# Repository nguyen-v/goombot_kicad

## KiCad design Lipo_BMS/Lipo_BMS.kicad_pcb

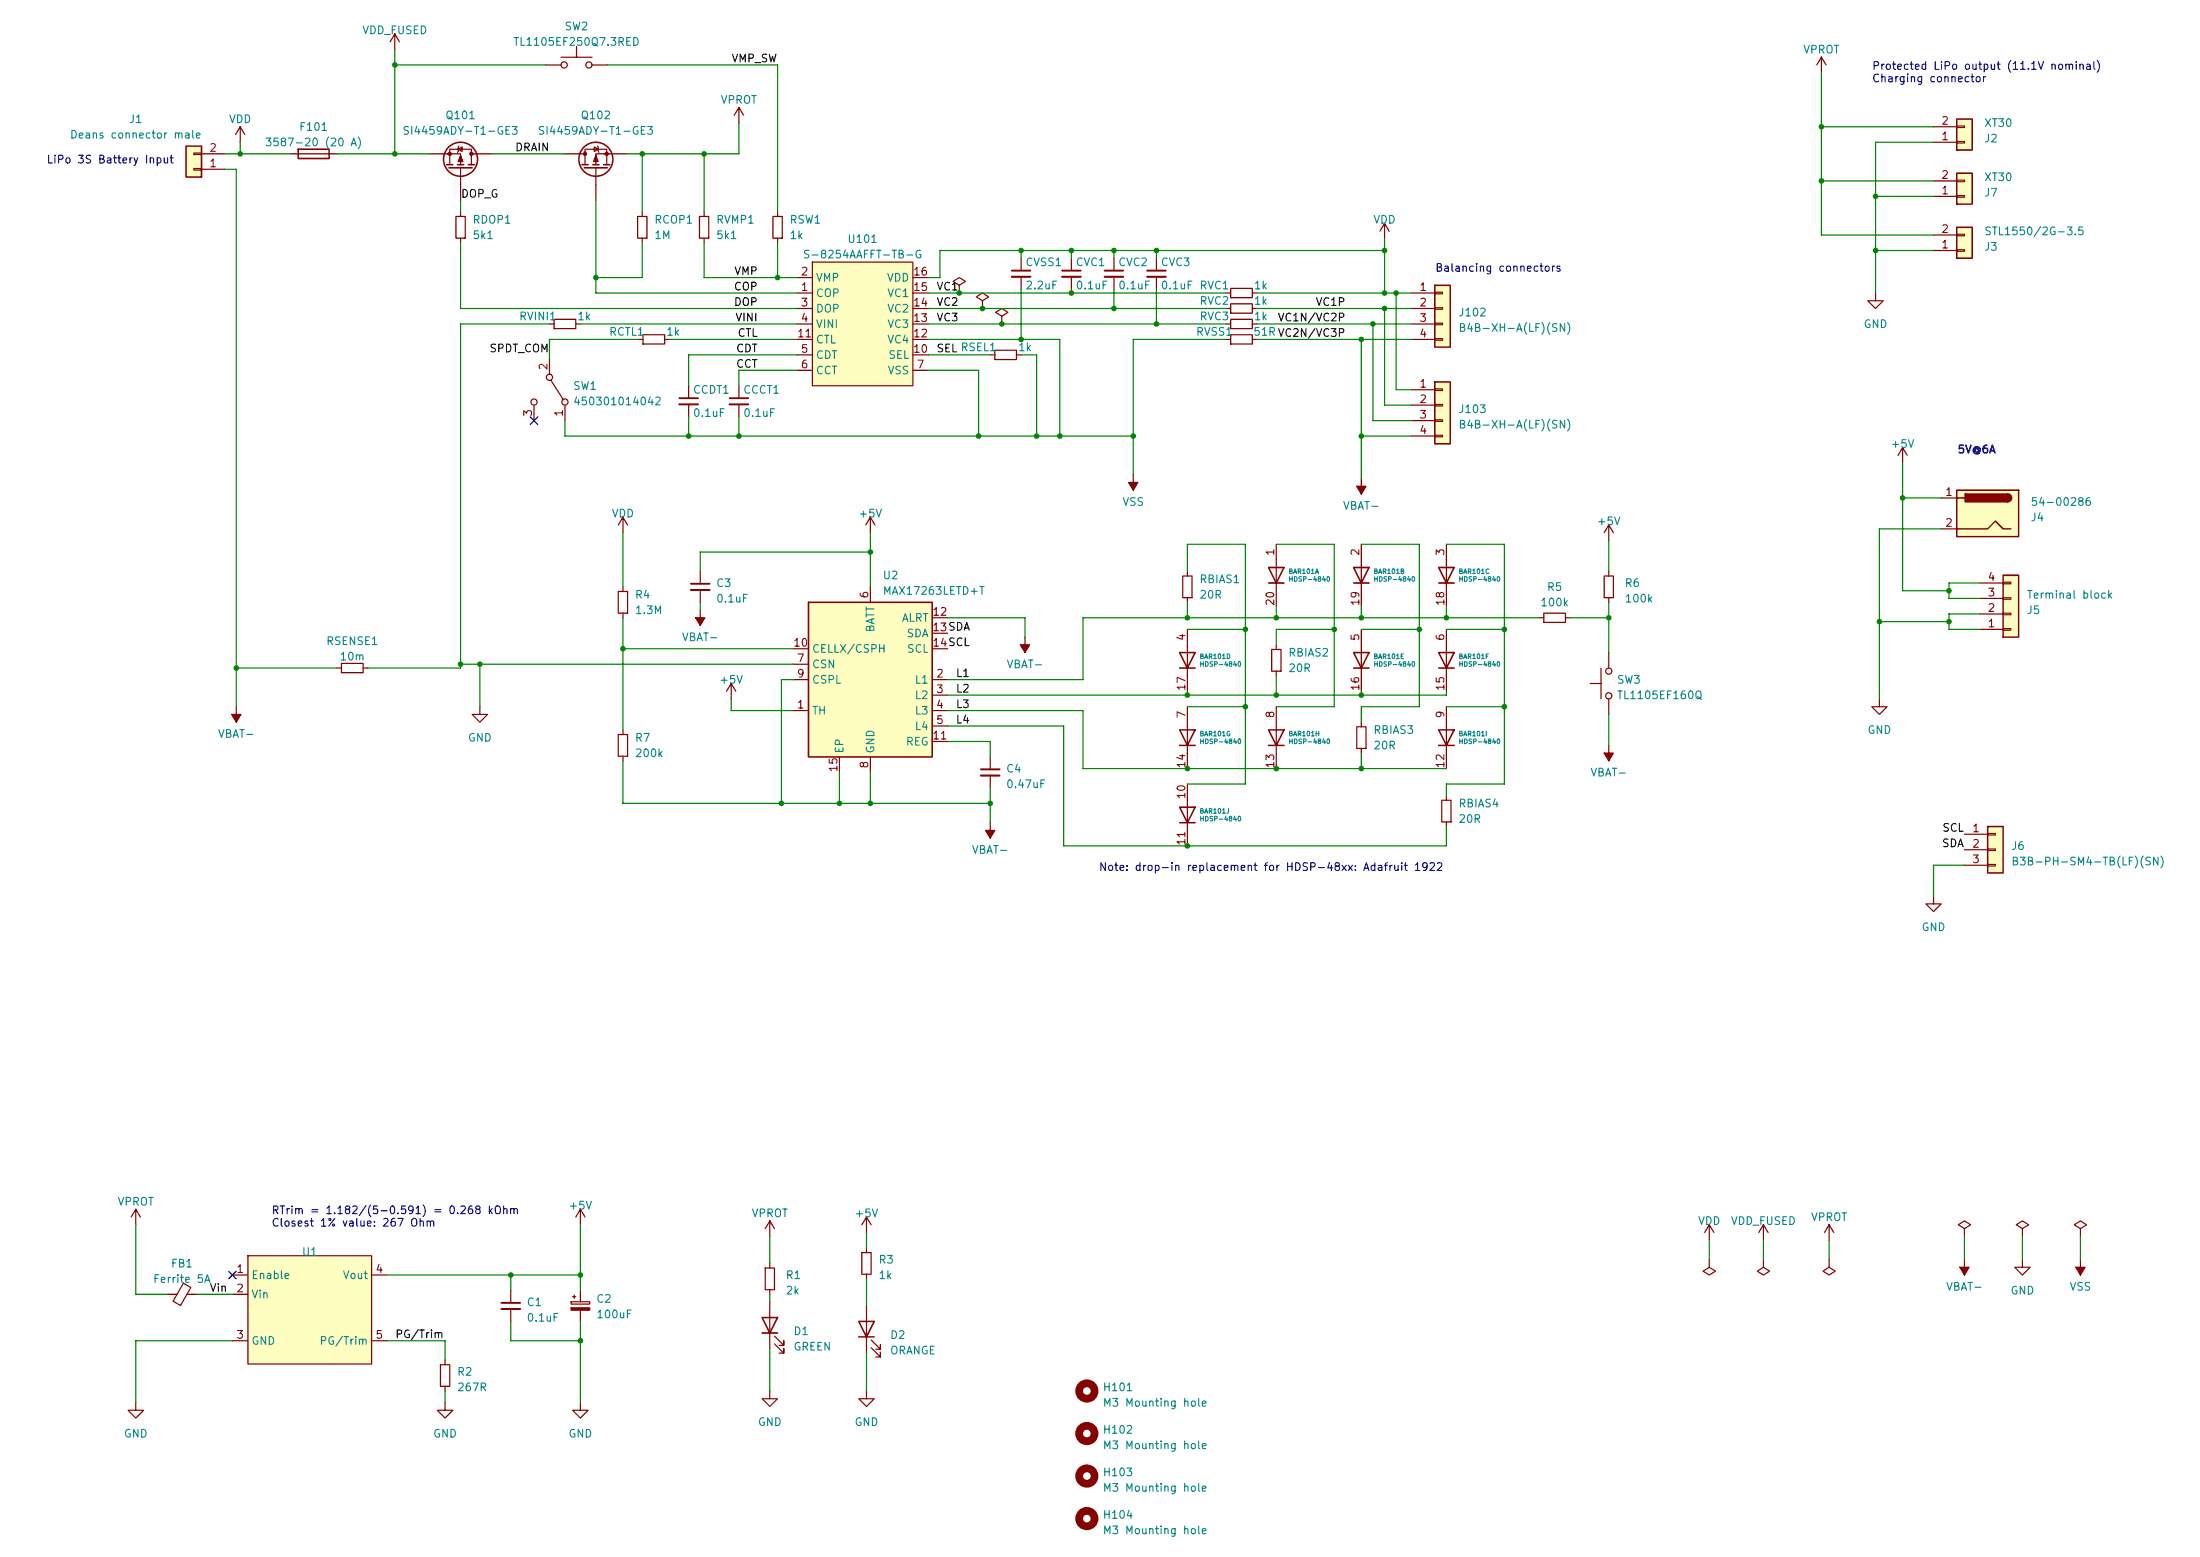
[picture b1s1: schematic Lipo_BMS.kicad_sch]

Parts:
BAR101: HDSP-4840
C1, C3: 0.1uF; C_0603_1608Metric
C2: 100uF; C_1210_3225Metric
C4: 0.47uF; C_0603_1608Metric
CCCT1: 0.1uF; C_0603_1608Metric
CCDT1: 0.1uF; C_0603_1608Metric
CVC1, CVC2, CVC3: 0.1uF; C_0603_1608Metric
CVSS1: 2.2uF; C_0603_1608Metric
D1: GREEN; LED_0603_1608Metric
D2: ORANGE; LED_0603_1608Metric
F101: 3587-20 (20 A); 3587
FB1: Ferrite 5A; L_0603_1608Metric
H101, H102, H103, H104: M3 Mounting hole; MountingHole_3.2mm_M3_Pad
J1: Deans connector male; DEANS
J2, J7: XT30; AMASS_XT30U-M_1x02_P5.0mm_Vertical
J3: STL1550/2G-3.5; STL1550-2
J4: 54-00286
J5: Terminal block; TerminalBlock_Phoenix_MPT-0,5-4-2.54_1x04_P2.54mm_Horizontal
J6: B3B-PH-SM4-TB(LF)(SN); JST_PH_B3B-PH-SM4-TB_1x03-1MP_P2.00mm_Vertical
J102, J103: B4B-XH-A(LF)(SN); JST_XH_B4B-XH-A_1x04_P2.50mm_Vertical
Q101, Q102: SI4459ADY-T1-GE3; SOIC-8_3.9x4.9mm_P1.27mm
R1: 2k; R_0603_1608Metric
R2: 267R; R_0603_1608Metric
R3: 1k; R_0603_1608Metric
R4: 1.3M; R_0603_1608Metric
R5, R6: 100k; R_0603_1608Metric
R7: 200k; R_0603_1608Metric
RBIAS1, RBIAS2, RBIAS3, RBIAS4: 20R; R_0603_1608Metric
RCOP1: 1M; R_0603_1608Metric
RCTL1: 1k; R_0603_1608Metric
RDOP1: 5k1; R_0603_1608Metric
RSEL1: 1k; R_0603_1608Metric
RSENSE1: 10m; R_1206_3216Metric
RSW1: 1k; R_0603_1608Metric
RVC1, RVC2, RVC3: 1k; R_0603_1608Metric
RVINI1: 1k; R_0603_1608Metric
RVMP1: 5k1; R_0603_1608Metric
RVSS1: 51R; R_0603_1608Metric
SW1: 450301014042
SW2: TL1105EF250Q7.3RED; SW_PUSH_6mm_H7.3mm
SW3: TL1105EF160Q; SW_PUSH_6mm_H7.3mm
U1: LDO06C-005W05-HJ
U2: MAX17263LETD+T; DFN-14-1EP_3x3mm_P0.4mm_EP1.78x2.35mm
U101: S-8254AAFFT-TB-G; TSSOP-16_4.4x5mm_P0.65mm

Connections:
+5V: C1.1, C2.1, C3.1, J4.1, J5.3, J5.4, R3.1, R6.2, U1.4 (Vout), U2.1 (TH), U2.6 (BATT)
/CCT: CCCT1.1, U101.6 (CCT)
/CDT: CCDT1.1, U101.5 (CDT)
/COP: Q102.4 (G), RCOP1.1, U101.1 (COP)
/CTL: RCTL1.2, U101.11 (CTL)
/DOP: RDOP1.1, U101.3 (DOP)
/DOP_G: Q101.4 (G), RDOP1.2
/DRAIN: Q101.5 (D), Q101.6 (D), Q101.7 (D), Q101.8 (D), Q102.5 (D), Q102.6 (D), Q102.7 (D), Q102.8 (D)
/L1: BAR101.18 (K), BAR101.19 (K), BAR101.20 (K), R5.1, RBIAS1.1, U2.2 (L1)
/L2: BAR101.15 (K), BAR101.16 (K), BAR101.17 (K), RBIAS2.1, U2.3 (L2)
/L3: BAR101.12 (K), BAR101.13 (K), BAR101.14 (K), RBIAS3.1, U2.4 (L3)
/L4: BAR101.11 (K), RBIAS4.1, U2.5 (L4)
/PG/Trim: R2.1, U1.5 (PG/Trim)
/SCL: J6.1, U2.14 (SCL)
/SDA: J6.2, U2.13 (SDA)
/SEL: RSEL1.1, U101.10 (SEL)
/SPDT_COM: RCTL1.1, SW1.2 (B)
/VC1: CVC1.2, RVC1.1, U101.15 (VC1)
/VC1N/VC2P: J102.3, J103.3, RVC3.2
/VC1P: J102.2, J103.2, RVC2.2
/VC2: CVC2.2, RVC2.1, U101.14 (VC2)
/VC3: CVC3.2, RVC3.1, U101.13 (VC3)
/VINI: RVINI1.2, U101.4 (VINI)
/VMP: RSW1.1, RVMP1.1, U101.2 (VMP)
/VMP_SW: RSW1.2, SW2.2
/Vin: FB1.2, U1.2 (Vin)
GND: C1.2, C2.2, D1.1 (K), D2.1 (K), J2.1, J3.1, J4.2, J5.1, J5.2, J6.3, J7.1, R2.2, RSENSE1.2, RVINI1.1, U1.3 (GND), U2.7 (CSN)
unnamed: BAR101.1 (A), BAR101.8 (A), RBIAS2.2
unnamed: BAR101.2 (A), BAR101.5 (A), RBIAS3.2
unnamed: BAR101.3 (A), BAR101.6 (A), BAR101.9 (A), RBIAS4.2
unnamed: BAR101.4 (A), BAR101.7 (A), BAR101.10 (A), RBIAS1.2
unnamed: D1.2 (A), R1.2
unnamed: D2.2 (A), R3.2
unnamed: R5.2, R6.1, SW3.2
unnamed: R4.1, R7.2, U2.10 (CELLX/CSPH)
unnamed: C4.1, U2.11 (REG)
VBAT-: C3.2, C4.2, J1.1, J102.4, J103.4, R7.1, RSENSE1.1, RVSS1.2, SW3.1, U2.8 (GND), U2.9 (CSPL), U2.12 (ALRT), U2.15 (EP)
VDD: CVC1.1, CVC2.1, CVC3.1, CVSS1.1, F101.1, F101.2, J1.2, J102.1, J103.1, R4.2, RVC1.2, U101.16 (VDD)
VDD_FUSED: F101.3, F101.4, Q101.1 (S), Q101.2 (S), Q101.3 (S), SW2.1
VPROT: FB1.1, J2.2, J3.2, J7.2, Q102.1 (S), Q102.2 (S), Q102.3 (S), R1.1, RCOP1.2, RVMP1.2
VSS: CCCT1.2, CCDT1.2, CVSS1.2, RSEL1.2, RVSS1.1, SW1.1 (A), U101.7 (VSS), U101.12 (VC4)

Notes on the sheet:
RTrim = 1.182/(5-0.591) = 0.268 kOhm Closest 1% value: 267 Ohm
5V@6A
Note: drop-in replacement for HDSP-48xx: Adafruit 1922
Balancing connectors
Protected LiPo output (11.1V nominal) Charging connector
LiPo 3S Battery Input

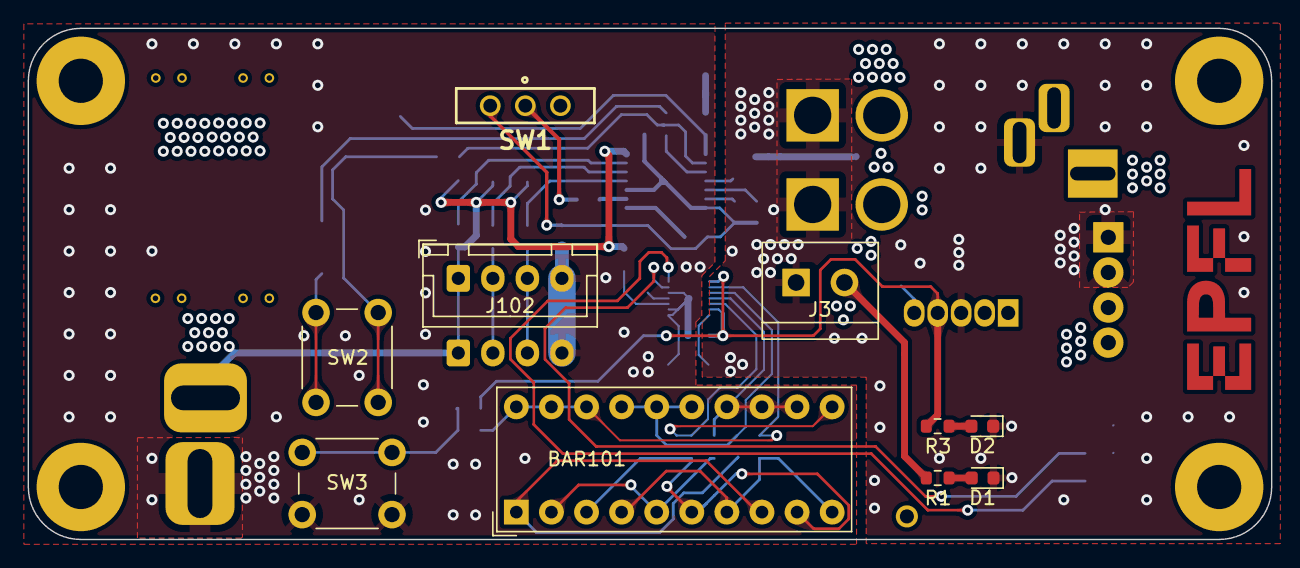
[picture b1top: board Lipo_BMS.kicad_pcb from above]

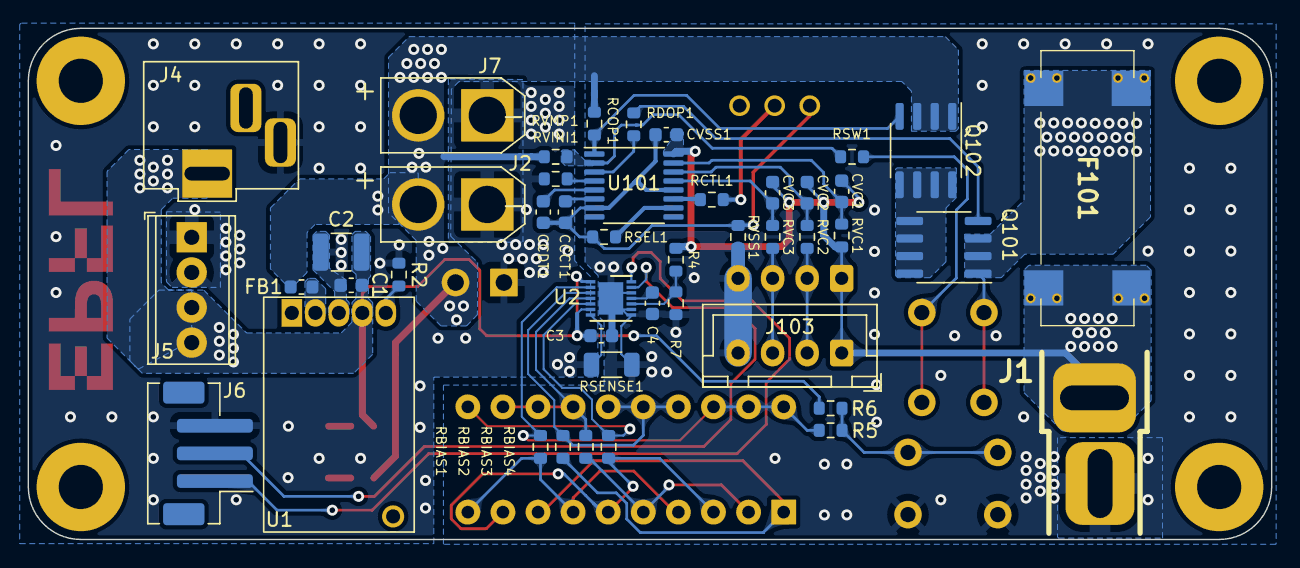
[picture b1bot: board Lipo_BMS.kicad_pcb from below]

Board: 2 copper layers, 90.0 x 37.0 mm, 81 parts (56 on the bottom side), 41 nets.

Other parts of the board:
kibuzzard-643EAC98: G***; kibuzzard-643EAC98
kibuzzard-643EACB8: G***; kibuzzard-643EACB8
kibuzzard-643EACE6, kibuzzard-643EACE6#2, kibuzzard-643EACE6#3, kibuzzard-643EACE6#4: G***; kibuzzard-643EACE6
kibuzzard-643EACF0, kibuzzard-643EACF0#2: G***; kibuzzard-643EACF0
kibuzzard-643EAD40: G***; kibuzzard-643EAD40
kibuzzard-643EADF2: G***; kibuzzard-643EADF2
kibuzzard-643EAE00: G***; kibuzzard-643EAE00
kibuzzard-643EAE23: G***; kibuzzard-643EAE23
kibuzzard-643EAF8C, kibuzzard-643EAF8C#2: G***; kibuzzard-643EAF8C
kibuzzard-643EAF9F, kibuzzard-643EAF9F#2, kibuzzard-643EAF9F#3: G***; kibuzzard-643EAF9F
kibuzzard-643EAF53: G***; kibuzzard-643EAF53
kibuzzard-643EAF61: G***; kibuzzard-643EAF61
kibuzzard-643EB03D: G***; kibuzzard-643EB03D
kibuzzard-643EEDF5: G***; kibuzzard-643EEDF5
kibuzzard-643EEE0C: G***; kibuzzard-643EEE0C

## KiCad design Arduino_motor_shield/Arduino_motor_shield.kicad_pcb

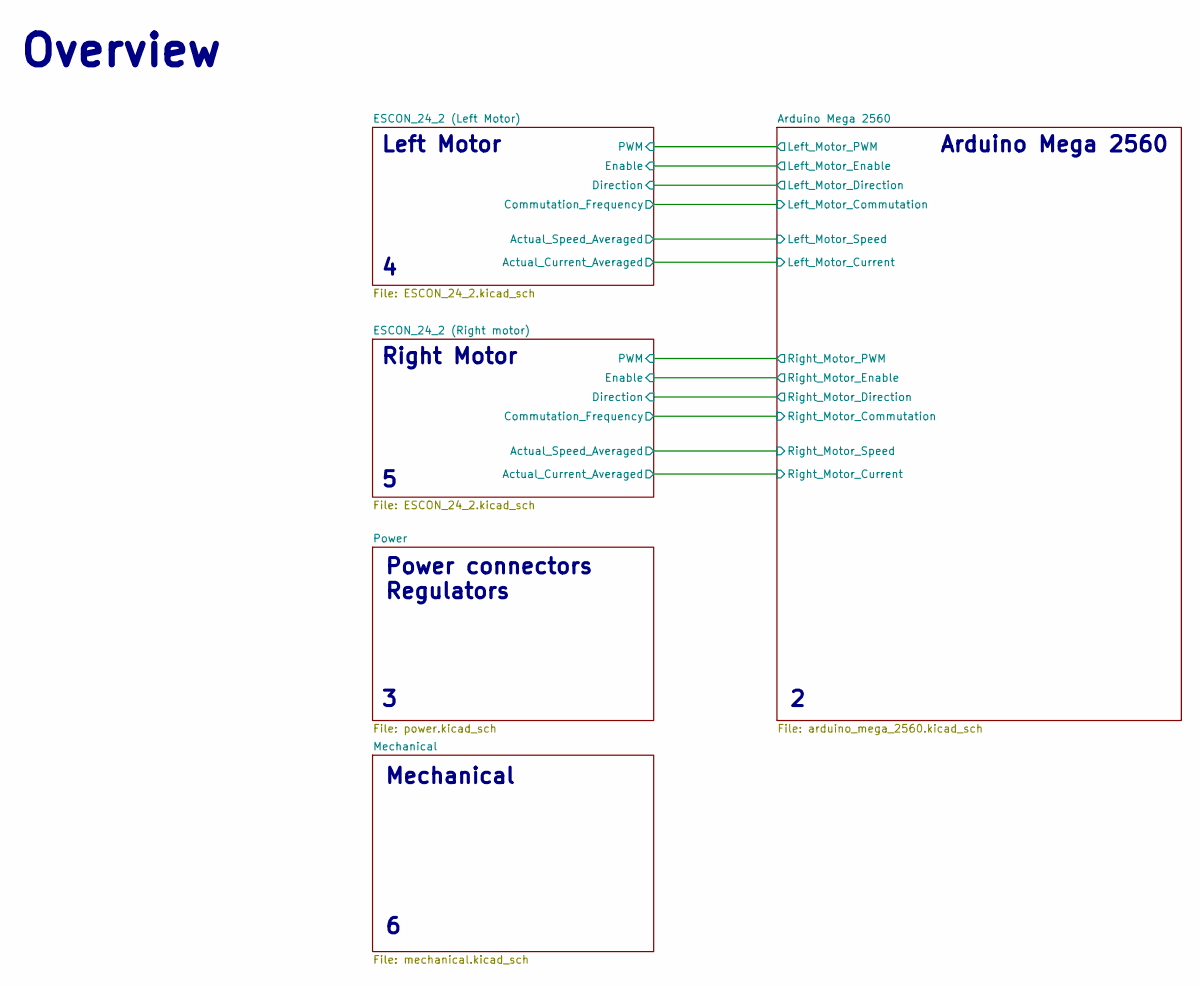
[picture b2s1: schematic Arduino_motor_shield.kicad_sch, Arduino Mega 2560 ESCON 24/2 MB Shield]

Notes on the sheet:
Mechanical
Overview
Right Motor
Arduino Mega 2560
Left Motor
Power connectors Regulators

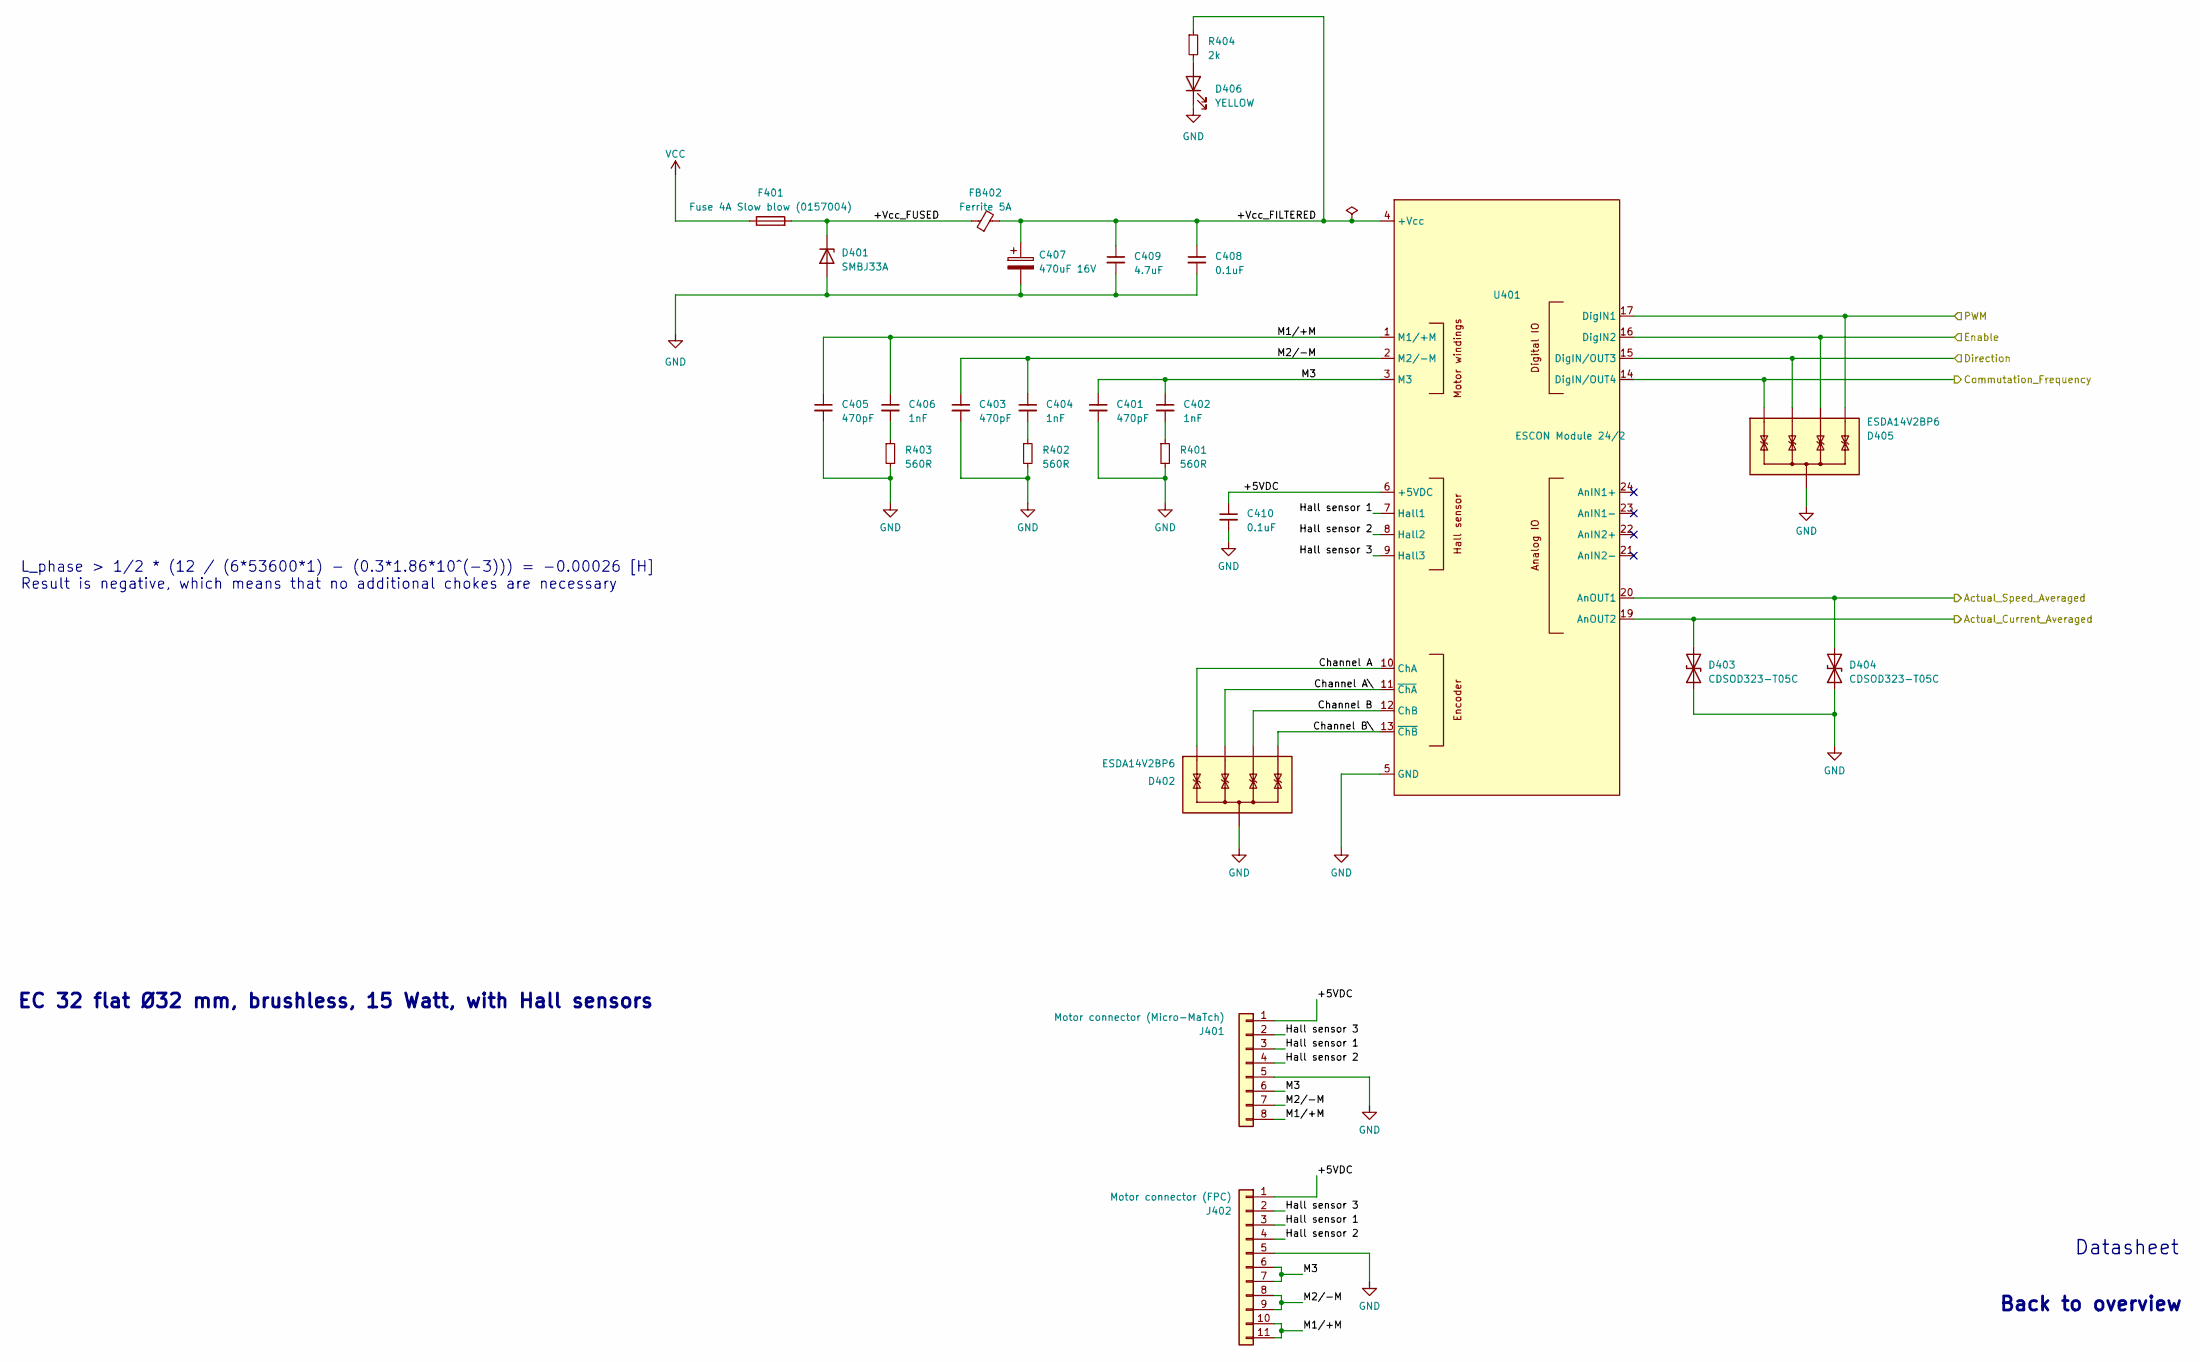
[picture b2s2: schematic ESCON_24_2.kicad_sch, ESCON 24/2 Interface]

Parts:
C401, C403, C405: 470pF; C_0603_1608Metric
C402, C404, C406: 1nF; C_0603_1608Metric
C407: 470uF 16V; C_Radial_D10.0mm_H16.0mm_P5.00mm
C408, C410: 0.1uF; C_0603_1608Metric
C409: 4.7uF; C_0603_1608Metric
D401: SMBJ33A; D_SMB
D402, D405: ESDA14V2BP6; SOT-666
D403, D404: CDSOD323-T05C; D_SOD-323_HandSoldering
D406: YELLOW; LED_0603_1608Metric
F401: Fuse 4A Slow blow (0157004); Fuseholder_Littelfuse_Nano2_157x
FB402: Ferrite 5A; L_0603_1608Metric
J401: Motor connector (Micro-MaTch); TE_7-215079-8
J402: Motor connector (FPC); TE_1-84953-1
R401, R402, R403: 560R; R_0603_1608Metric
R404: 2k; R_0603_1608Metric
U401: ESCON Module 24/2; ESCON 24_5 Module

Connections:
/Arduino Mega 2560/Left_Motor_Commutation: D405.1 (IO1), U401.14 (DigIN/OUT4); also elsewhere on the board
/Arduino Mega 2560/Left_Motor_Current: D403.2 (A2), U401.19 (AnOUT2); also elsewhere on the board
/Arduino Mega 2560/Left_Motor_Direction: D405.3 (IO2), U401.15 (DigIN/OUT3); also elsewhere on the board
/Arduino Mega 2560/Left_Motor_Enable: D405.4 (IO3), U401.16 (DigIN2); also elsewhere on the board
/Arduino Mega 2560/Left_Motor_PWM: D405.6 (IO4), U401.17 (DigIN1); also elsewhere on the board
/Arduino Mega 2560/Left_Motor_Speed: D404.2 (A2), U401.20 (AnOUT1); also elsewhere on the board
/ESCON_24_2 (Left Motor)/+5VDC: C410.1, J401.1, J402.1, U401.6 (+5VDC)
/ESCON_24_2 (Left Motor)/+Vcc_FILTERED: C407.1, C408.1, C409.1, FB402.2, R404.1, U401.4 (+Vcc)
/ESCON_24_2 (Left Motor)/+Vcc_FUSED: D401.1 (K), F401.2, FB402.1
/ESCON_24_2 (Left Motor)/Channel A: D402.1 (IO1), U401.10 (ChA)
/ESCON_24_2 (Left Motor)/Channel A\: D402.3 (IO2), U401.11 (~ChA)
/ESCON_24_2 (Left Motor)/Channel B: D402.4 (IO3), U401.12 (ChB)
/ESCON_24_2 (Left Motor)/Channel B\: D402.6 (IO4), U401.13 (~ChB)
/ESCON_24_2 (Left Motor)/Hall sensor 1: J401.3, J402.3, U401.7 (Hall1)
/ESCON_24_2 (Left Motor)/Hall sensor 2: J401.4, J402.4, U401.8 (Hall2)
/ESCON_24_2 (Left Motor)/Hall sensor 3: J401.2, J402.2, U401.9 (Hall3)
/ESCON_24_2 (Left Motor)/M1/+M: C405.1, C406.1, J401.8, J402.10, J402.11, U401.1 (M1/+M)
/ESCON_24_2 (Left Motor)/M2/-M: C403.1, C404.1, J401.7, J402.8, J402.9, U401.2 (M2/-M)
/ESCON_24_2 (Left Motor)/M3: C401.1, C402.1, J401.6, J402.6, J402.7, U401.3 (M3)
unnamed: C402.2, R401.1
unnamed: C404.2, R402.1
unnamed: C406.2, R403.1
unnamed: D406.2 (A), R404.2
VCC: F401.1; also elsewhere on the board

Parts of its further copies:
C501, C503, C506: 470pF; C_0603_1608Metric
C502, C505, C508: 1nF; C_0603_1608Metric
C504: 470uF 16V; C_Radial_D10.0mm_H16.0mm_P5.00mm
C507: 4.7uF; C_0603_1608Metric
C509, C510: 0.1uF; C_0603_1608Metric
D501: SMBJ33A; D_SMB
D502, D505: ESDA14V2BP6; SOT-666
D503, D504: CDSOD323-T05C; D_SOD-323_HandSoldering
D506: YELLOW; LED_0603_1608Metric
F501: Fuse 4A Slow blow (0157004); Fuseholder_Littelfuse_Nano2_157x
FB502: Ferrite 5A; L_0603_1608Metric
J501: Motor connector (Micro-MaTch); TE_7-215079-8
J502: Motor connector (FPC); TE_1-84953-1
R501, R502, R503: 560R; R_0603_1608Metric
R504: 2k; R_0603_1608Metric
U501: ESCON Module 24/2; ESCON 24_5 Module

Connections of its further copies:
/Arduino Mega 2560/Right_Motor_Commutation: D505.1 (IO1), U501.14 (DigIN/OUT4); also elsewhere on the board
/Arduino Mega 2560/Right_Motor_Current: D503.2 (A2), U501.19 (AnOUT2); also elsewhere on the board
/Arduino Mega 2560/Right_Motor_Direction: D505.3 (IO2), U501.15 (DigIN/OUT3); also elsewhere on the board
/Arduino Mega 2560/Right_Motor_Enable: D505.4 (IO3), U501.16 (DigIN2); also elsewhere on the board
/Arduino Mega 2560/Right_Motor_PWM: D505.6 (IO4), U501.17 (DigIN1); also elsewhere on the board
/Arduino Mega 2560/Right_Motor_Speed: D504.2 (A2), U501.20 (AnOUT1); also elsewhere on the board
/ESCON_24_2 (Right motor)/+5VDC: C510.1, J501.1, J502.1, U501.6 (+5VDC)
/ESCON_24_2 (Right motor)/+Vcc_FILTERED: C504.1, C507.1, C509.1, FB502.2, R504.1, U501.4 (+Vcc)
/ESCON_24_2 (Right motor)/+Vcc_FUSED: D501.1 (K), F501.2, FB502.1
/ESCON_24_2 (Right motor)/Channel A: D502.1 (IO1), U501.10 (ChA)
/ESCON_24_2 (Right motor)/Channel A\: D502.3 (IO2), U501.11 (~ChA)
/ESCON_24_2 (Right motor)/Channel B: D502.4 (IO3), U501.12 (ChB)
/ESCON_24_2 (Right motor)/Channel B\: D502.6 (IO4), U501.13 (~ChB)
/ESCON_24_2 (Right motor)/Hall sensor 1: J501.3, J502.3, U501.7 (Hall1)
/ESCON_24_2 (Right motor)/Hall sensor 2: J501.4, J502.4, U501.8 (Hall2)
/ESCON_24_2 (Right motor)/Hall sensor 3: J501.2, J502.2, U501.9 (Hall3)
/ESCON_24_2 (Right motor)/M1/+M: C501.1, C502.1, J501.8, J502.10, J502.11, U501.1 (M1/+M)
/ESCON_24_2 (Right motor)/M2/-M: C503.1, C505.1, J501.7, J502.8, J502.9, U501.2 (M2/-M)
/ESCON_24_2 (Right motor)/M3: C506.1, C508.1, J501.6, J502.6, J502.7, U501.3 (M3)
unnamed: C502.2, R501.1
unnamed: C505.2, R502.1
unnamed: C508.2, R503.1
unnamed: D506.2 (A), R504.2
VCC: F501.1; also elsewhere on the board

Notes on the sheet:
Back to overview
L_phase > 1/2 * (12 / (6*53600*1) - (0.3*1.86*10^(-3))) = -0.00026 [H] Result is negative, which means that no additional chokes are necessary
Datasheet
EC 32 flat Ø32 mm, brushless, 15 Watt, with Hall sensors

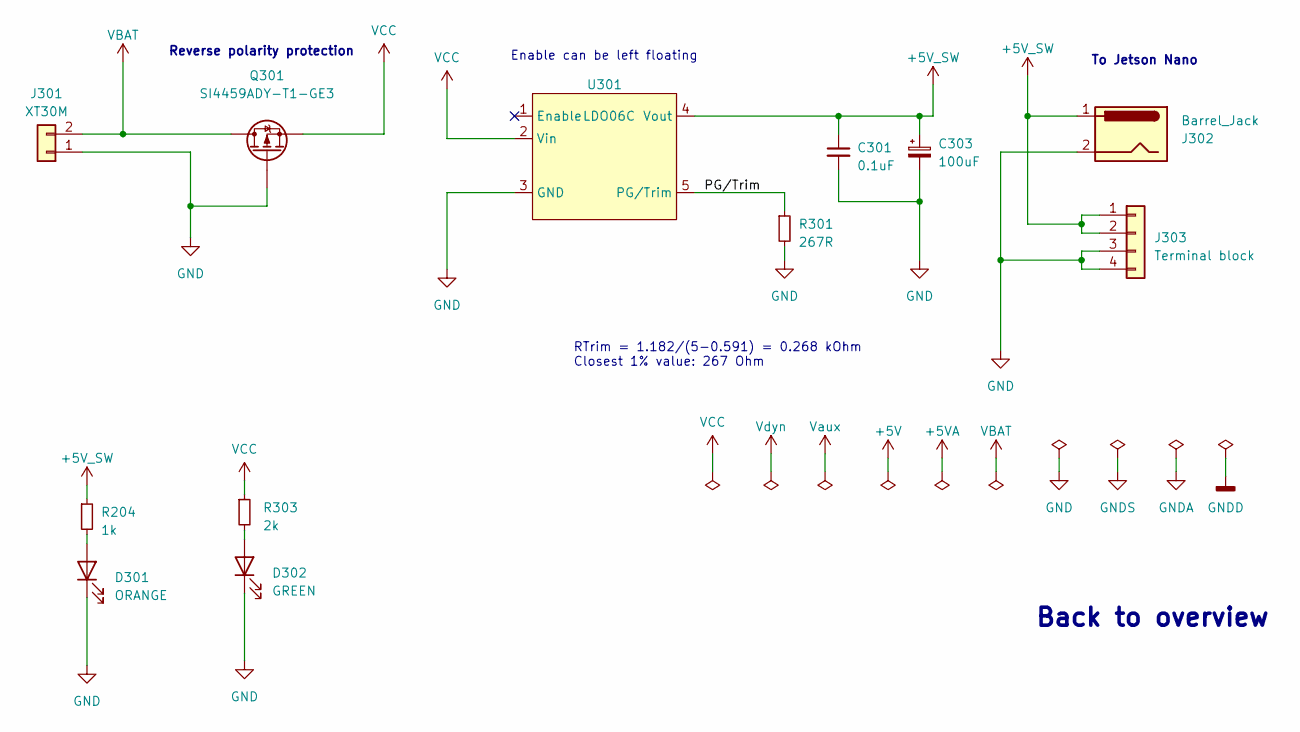
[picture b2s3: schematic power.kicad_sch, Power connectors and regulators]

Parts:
C301: 0.1uF; C_0603_1608Metric
C303: 100uF; C_1210_3225Metric
D301: ORANGE; LED_0603_1608Metric
D302: GREEN; LED_0603_1608Metric
J301: XT30M; AMASS_XT30U-M_1x02_P5.0mm_Vertical
J302: Barrel_Jack; BarrelJack_Horizontal
J303: Terminal block; TerminalBlock_Phoenix_MPT-0,5-4-2.54_1x04_P2.54mm_Horizontal
Q301: SI4459ADY-T1-GE3; SOIC-8_3.9x4.9mm_P1.27mm
R204: 1k; R_0603_1608Metric
R301: 267R; R_0603_1608Metric
R303: 2k; R_0603_1608Metric
U301: LDO06C; LDO06C-005W05-HJ

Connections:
/Power/PG/Trim: R301.1, U301.5 (PG/Trim)
unnamed: D302.2 (A), R303.2
VBAT: J301.2, Q301.5 (D), Q301.6 (D), Q301.7 (D), Q301.8 (D)
VCC: Q301.1 (S), Q301.2 (S), Q301.3 (S), R303.1, U301.2 (Vin); also elsewhere on the board

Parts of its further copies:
R302: 1k; R_0603_1608Metric

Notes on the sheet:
Enable can be left floating
To Jetson Nano
Back to overview
RTrim = 1.182/(5-0.591) = 0.268 kOhm Closest 1% value: 267 Ohm
Reverse polarity protection

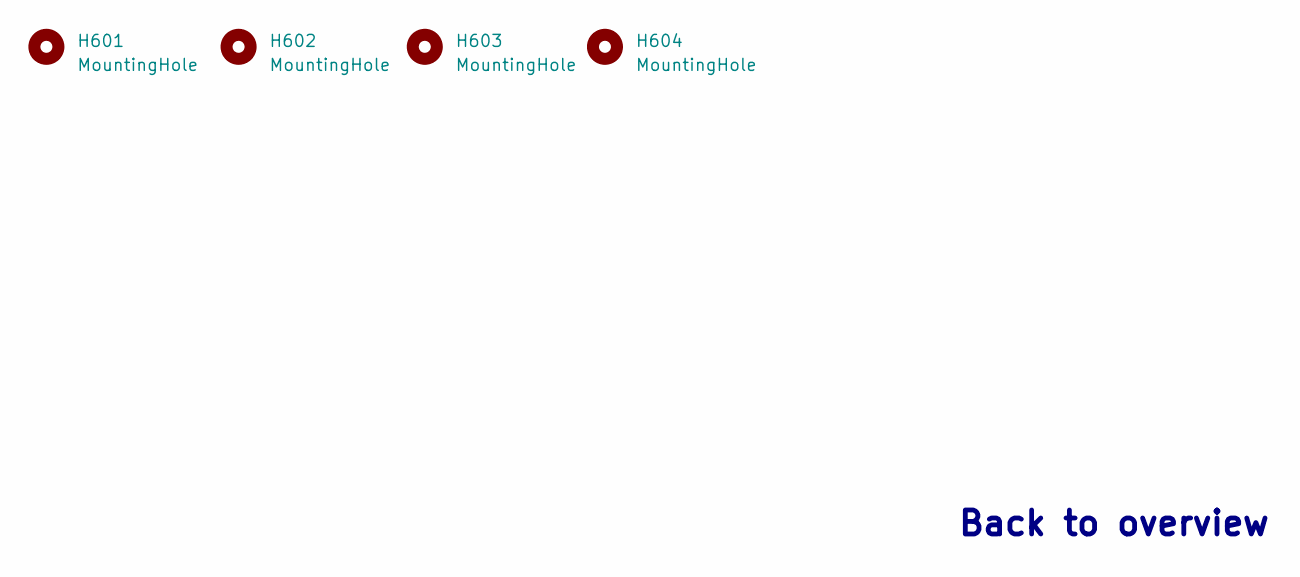
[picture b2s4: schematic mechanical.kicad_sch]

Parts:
H601, H602, H603, H604: MountingHole; MountingHole_3.2mm_M3_Pad

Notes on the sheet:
Back to overview
